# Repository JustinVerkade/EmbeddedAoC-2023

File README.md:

# Embedded-AoC "Yuki"<br />
<br />

## Todo<br />
-> Add ESP32 bootloader function in vcom user interface for remote programming.<br />
-> Add system check for ESP32.<br />

## Completed<br />
-> Added a malloc/calloc/clrmem functions to allocate memory from the SRAM block.<br />
-> Configured FMC and linker to include the external memory as SRAM block.<br />
-> Added vcom enable variable so the system can respond to being opend as port.<br />
-> Added intermediate usb layer as the transmit function failed when bizzy without feedback.<br />
-> f_debug function to log FatFs problems to vcom interface.<br />
-> Added system check for SD card.<br />
-> Added system check for SRAM memory.<br />
-> Added system structure for executing AoC puzzles.<br />

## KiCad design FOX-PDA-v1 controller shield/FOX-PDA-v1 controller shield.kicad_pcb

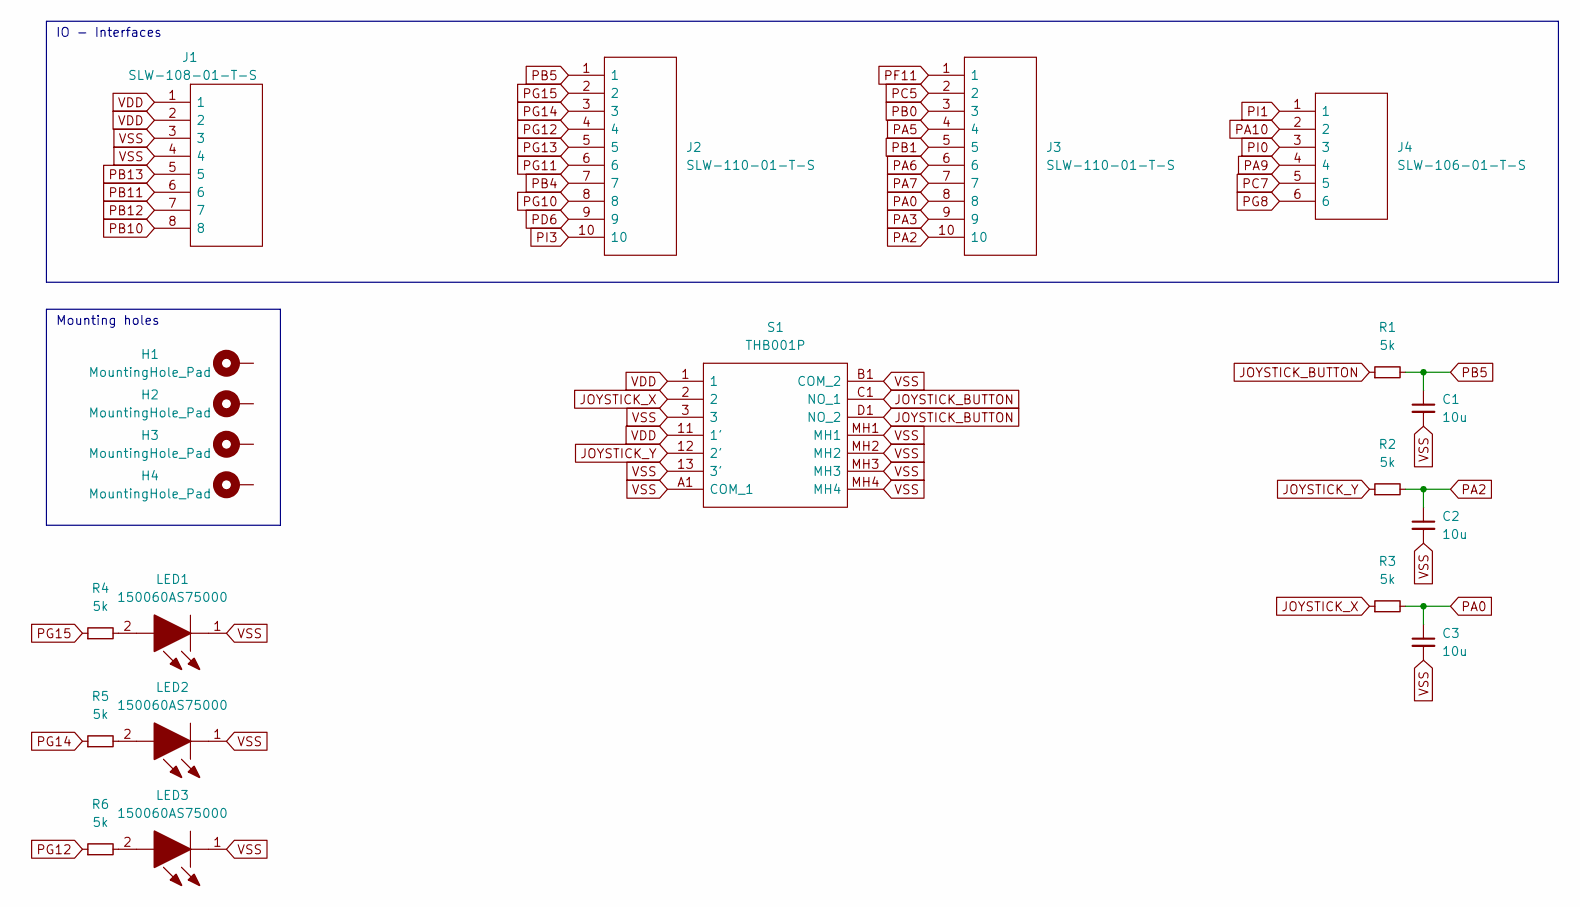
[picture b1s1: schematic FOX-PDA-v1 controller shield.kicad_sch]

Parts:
C1, C2, C3: 10u; C_0805_2012Metric
H1, H2, H3, H4: MountingHole_Pad; MountingHole_3.2mm_M3_Pad_Via
J1: SLW-108-01-T-S; SLW-108-01-X-S; Mouser Part Number 200-SLW10801TS
J2, J3: SLW-110-01-T-S; SLW-110-01-X-S; Mouser Part Number 200-SLW11001TS
J4: SLW-106-01-T-S; SLW-106-01-X-S; Mouser Part Number 200-SLW10601TS
LED1, LED2, LED3: 150060AS75000; LEDC1608X80N; Mouser Part Number 710-150060AS75000
R1, R2, R3, R4, R5, R6: 5k; R_0805_2012Metric
S1: THB001P; Mouser Part Number 611-THB001P

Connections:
JOYSTICK_BUTTON: R1.1, S1.C1 (NO_1), S1.D1 (NO_2)
JOYSTICK_X: R3.1, S1.2
JOYSTICK_Y: R2.1, S1.12 (2')
unnamed: LED1.2, R4.2
unnamed: LED2.2, R5.2
unnamed: LED3.2, R6.2
PA0: C3.1, J3.8, R3.2
PA2: C2.1, J3.10, R2.2
PA3: J3.9
PA5: J3.4
PA6: J3.6
PA7: J3.7
PA9: J4.4
PA10: J4.2
PB0: J3.3
PB1: J3.5
PB4: J2.7
PB5: C1.1, J2.1, R1.2
PB10: J1.8
PB11: J1.6
PB12: J1.7
PB13: J1.5
PC5: J3.2
PC7: J4.5
PD6: J2.9
PF11: J3.1
PG8: J4.6
PG10: J2.8
PG11: J2.6
PG12: J2.4, R6.1
PG13: J2.5
PG14: J2.3, R5.1
PG15: J2.2, R4.1
PI0: J4.3
PI1: J4.1
PI3: J2.10
VDD: J1.1, J1.2, S1.1, S1.11 (1')
VSS: C1.2, C2.2, C3.2, J1.3, J1.4, LED1.1, LED2.1, LED3.1, S1.3, S1.13 (3'), S1.A1 (COM_1), S1.B1 (COM_2), S1.MH1, S1.MH2, S1.MH3, S1.MH4

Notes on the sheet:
IO - Interfaces
Mounting holes

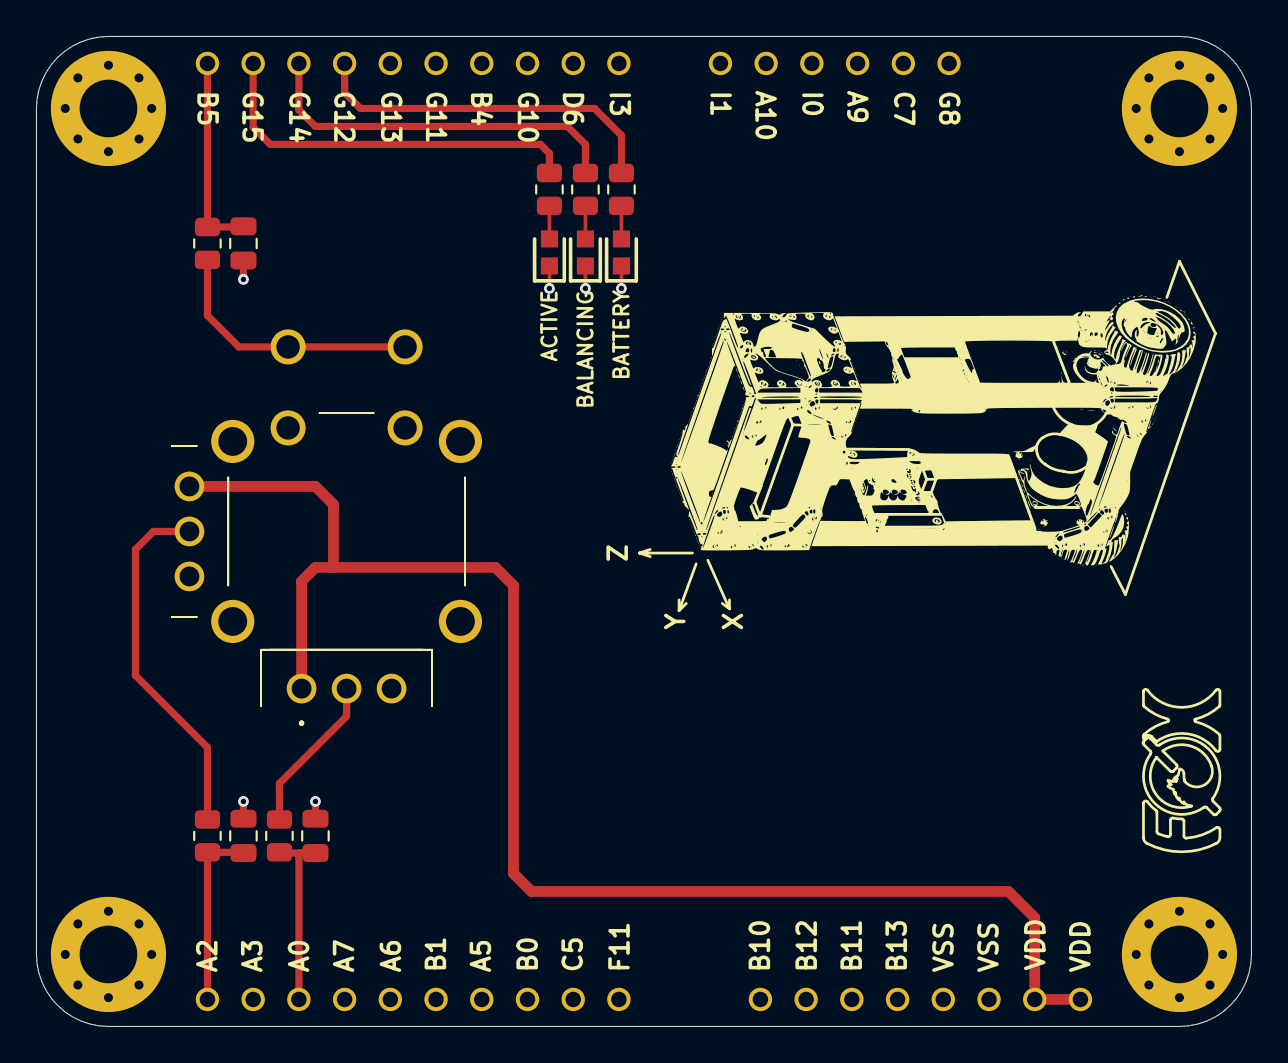
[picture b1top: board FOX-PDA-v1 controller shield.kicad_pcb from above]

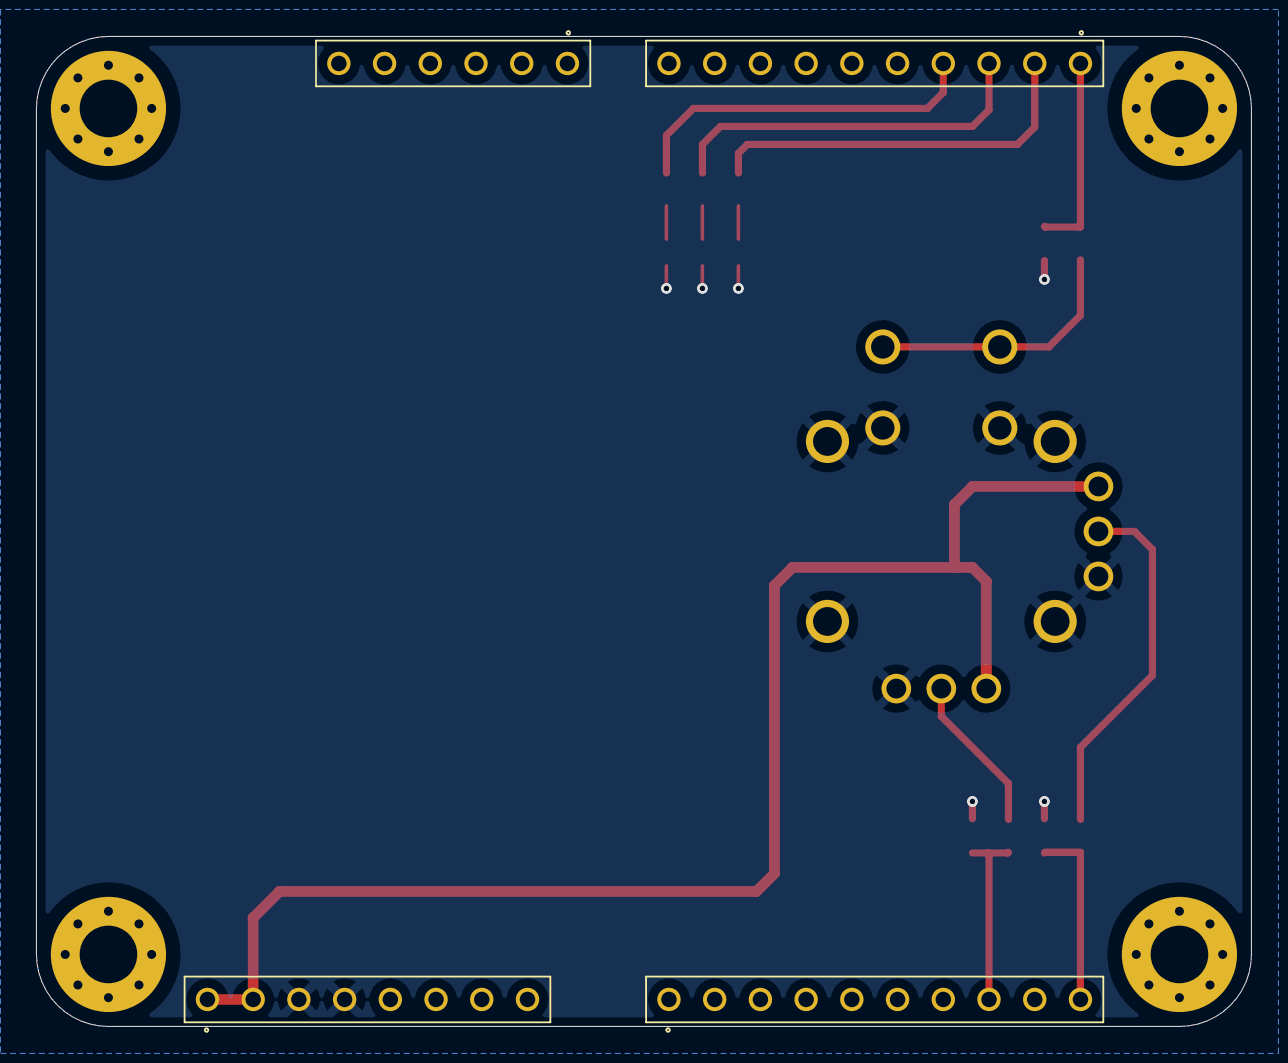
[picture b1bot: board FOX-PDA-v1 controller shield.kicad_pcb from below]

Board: 2 copper layers, 67.5 x 55.0 mm, 21 parts (4 on the bottom side), 14 nets.

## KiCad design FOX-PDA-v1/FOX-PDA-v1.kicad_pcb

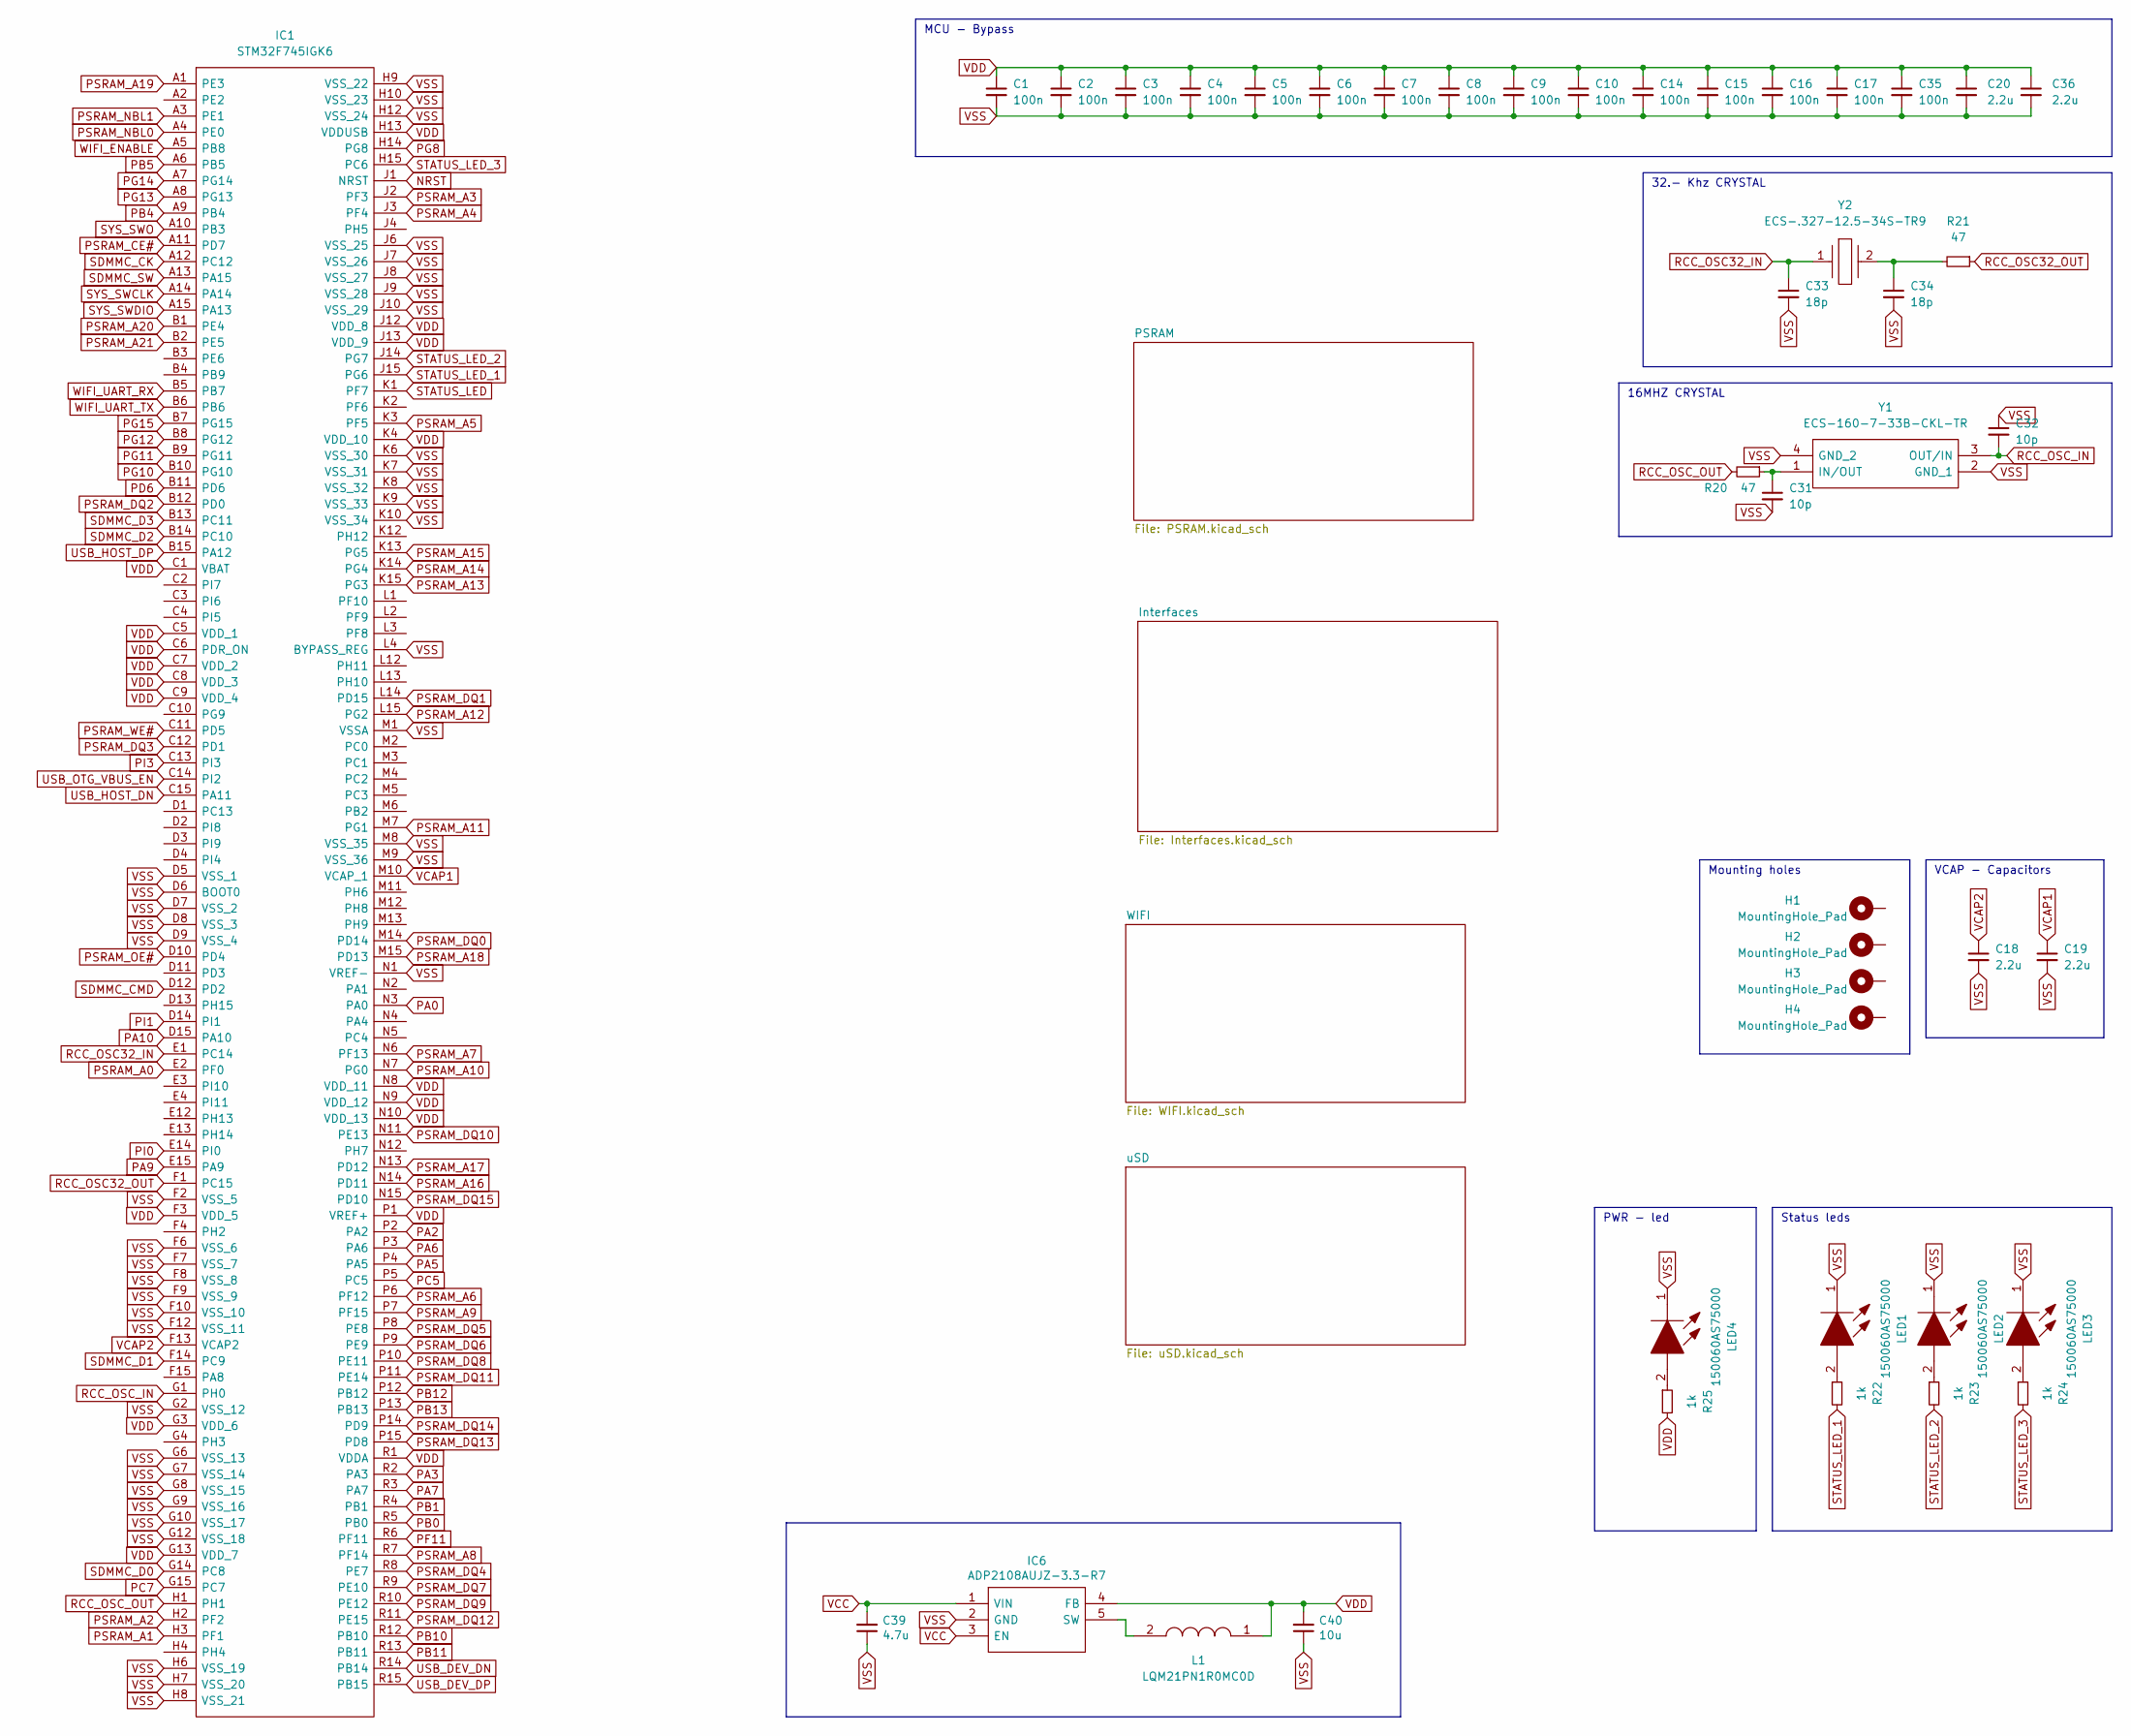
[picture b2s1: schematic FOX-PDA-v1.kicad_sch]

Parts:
C1, C2, C3, C4, C5, C6, C7, C8, C9, C10, C14, C15, C16, C17, C35: 100n; C_0402_1005Metric
C18, C19: 2.2u; C_0402_1005Metric
C20, C36: 2.2u; C_0603_1608Metric
C31, C32: 10p; C_0402_1005Metric
C33, C34: 18p; C_0402_1005Metric
C39: 4.7u; C_0603_1608Metric
C40: 10u; C_0603_1608Metric
H1, H2, H3, H4: MountingHole_Pad; MountingHole_3.2mm_M3_Pad_Via
IC1: STM32F745IGK6; BGA201C65P15X15_1000X1000X60; Mouser Part Number 511-STM32F745IGK6
IC6: ADP2108AUJZ-3.3-R7; SOT95P280X100-5N; Mouser Part Number 584-ADP2108AUJZ3.3R7
L1: LQM21PN1R0MC0D; Mouser Part Number 81-LQM21PN1R0MC0D
LED1, LED2, LED3, LED4: 150060AS75000; LEDC1608X80N; Mouser Part Number 710-150060AS75000
R20, R21: 47; R_0402_1005Metric
R22, R23, R24, R25: 1k; R_0402_1005Metric
Y1: ECS-160-7-33B-CKL-TR; ECS160733BCKLTR; Manufacturer_Part_Number ECS-160-7-33B-CKL-TR
Y2: ECS-.327-12.5-34S-TR9; ECS32712534STR9; Mouser Part Number 520-ECS-32712534STR9

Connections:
NRST: IC1.J1 (NRST); also elsewhere on the board
unnamed: C31.1, R20.1, Y1.1 (IN/OUT)
unnamed: C34.1, R21.2, Y2.2
unnamed: IC6.5 (SW), L1.2
unnamed: LED1.2, R22.1
unnamed: LED2.2, R23.1
unnamed: LED3.2, R24.1
unnamed: LED4.2, R25.1
PA0: IC1.N3 (PA0); also elsewhere on the board
PA2: IC1.P2 (PA2); also elsewhere on the board
PA3: IC1.R2 (PA3); also elsewhere on the board
PA5: IC1.P4 (PA5); also elsewhere on the board
PA6: IC1.P3 (PA6); also elsewhere on the board
PA7: IC1.R3 (PA7); also elsewhere on the board
PA9: IC1.E15 (PA9); also elsewhere on the board
PA10: IC1.D15 (PA10); also elsewhere on the board
PB0: IC1.R5 (PB0); also elsewhere on the board
PB1: IC1.R4 (PB1); also elsewhere on the board
PB4: IC1.A9 (PB4); also elsewhere on the board
PB5: IC1.A6 (PB5); also elsewhere on the board
PB10: IC1.R12 (PB10); also elsewhere on the board
PB11: IC1.R13 (PB11); also elsewhere on the board
PB12: IC1.P12 (PB12); also elsewhere on the board
PB13: IC1.P13 (PB13); also elsewhere on the board
PC5: IC1.P5 (PC5); also elsewhere on the board
PC7: IC1.G15 (PC7); also elsewhere on the board
PD6: IC1.B11 (PD6); also elsewhere on the board
PF11: IC1.R6 (PF11); also elsewhere on the board
PG8: IC1.H14 (PG8); also elsewhere on the board
PG10: IC1.B10 (PG10); also elsewhere on the board
PG11: IC1.B9 (PG11); also elsewhere on the board
PG12: IC1.B8 (PG12); also elsewhere on the board
PG13: IC1.A8 (PG13); also elsewhere on the board
PG14: IC1.A7 (PG14); also elsewhere on the board
PG15: IC1.B7 (PG15); also elsewhere on the board
PI0: IC1.E14 (PI0); also elsewhere on the board
PI1: IC1.D14 (PI1); also elsewhere on the board
PI3: IC1.C13 (PI3); also elsewhere on the board
PSRAM_A0: IC1.E2 (PF0); also elsewhere on the board
PSRAM_A1: IC1.H3 (PF1); also elsewhere on the board
PSRAM_A2: IC1.H2 (PF2); also elsewhere on the board
PSRAM_A3: IC1.J2 (PF3); also elsewhere on the board
PSRAM_A4: IC1.J3 (PF4); also elsewhere on the board
PSRAM_A5: IC1.K3 (PF5); also elsewhere on the board
PSRAM_A6: IC1.P6 (PF12); also elsewhere on the board
PSRAM_A7: IC1.N6 (PF13); also elsewhere on the board
PSRAM_A8: IC1.R7 (PF14); also elsewhere on the board
PSRAM_A9: IC1.P7 (PF15); also elsewhere on the board
PSRAM_A10: IC1.N7 (PG0); also elsewhere on the board
PSRAM_A11: IC1.M7 (PG1); also elsewhere on the board
PSRAM_A12: IC1.L15 (PG2); also elsewhere on the board
PSRAM_A13: IC1.K15 (PG3); also elsewhere on the board
PSRAM_A14: IC1.K14 (PG4); also elsewhere on the board
PSRAM_A15: IC1.K13 (PG5); also elsewhere on the board
PSRAM_A16: IC1.N14 (PD11); also elsewhere on the board
PSRAM_A17: IC1.N13 (PD12); also elsewhere on the board
PSRAM_A18: IC1.M15 (PD13); also elsewhere on the board
PSRAM_A19: IC1.A1 (PE3); also elsewhere on the board
PSRAM_A20: IC1.B1 (PE4); also elsewhere on the board
PSRAM_A21: IC1.B2 (PE5); also elsewhere on the board
PSRAM_CE#: IC1.A11 (PD7); also elsewhere on the board
PSRAM_DQ0: IC1.M14 (PD14); also elsewhere on the board
PSRAM_DQ1: IC1.L14 (PD15); also elsewhere on the board
PSRAM_DQ2: IC1.B12 (PD0); also elsewhere on the board
PSRAM_DQ3: IC1.C12 (PD1); also elsewhere on the board
PSRAM_DQ4: IC1.R8 (PE7); also elsewhere on the board
PSRAM_DQ5: IC1.P8 (PE8); also elsewhere on the board
PSRAM_DQ6: IC1.P9 (PE9); also elsewhere on the board
PSRAM_DQ7: IC1.R9 (PE10); also elsewhere on the board
PSRAM_DQ8: IC1.P10 (PE11); also elsewhere on the board
PSRAM_DQ9: IC1.R10 (PE12); also elsewhere on the board
PSRAM_DQ10: IC1.N11 (PE13); also elsewhere on the board
PSRAM_DQ11: IC1.P11 (PE14); also elsewhere on the board
PSRAM_DQ12: IC1.R11 (PE15); also elsewhere on the board
PSRAM_DQ13: IC1.P15 (PD8); also elsewhere on the board
PSRAM_DQ14: IC1.P14 (PD9); also elsewhere on the board
PSRAM_DQ15: IC1.N15 (PD10); also elsewhere on the board
PSRAM_NBL0: IC1.A4 (PE0); also elsewhere on the board
PSRAM_NBL1: IC1.A3 (PE1); also elsewhere on the board
PSRAM_OE#: IC1.D10 (PD4); also elsewhere on the board
PSRAM_WE#: IC1.C11 (PD5); also elsewhere on the board
RCC_OSC32_IN: C33.1, IC1.E1 (PC14), Y2.1
RCC_OSC32_OUT: IC1.F1 (PC15), R21.1
RCC_OSC_IN: C32.2, IC1.G1 (PH0), Y1.3 (OUT/IN)
RCC_OSC_OUT: IC1.H1, R20.2
SDMMC_CK: IC1.A12 (PC12); also elsewhere on the board
SDMMC_CMD: IC1.D12 (PD2); also elsewhere on the board
SDMMC_D0: IC1.G14 (PC8); also elsewhere on the board
SDMMC_D1: IC1.F14 (PC9); also elsewhere on the board
SDMMC_D2: IC1.B14 (PC10); also elsewhere on the board
SDMMC_D3: IC1.B13 (PC11); also elsewhere on the board
SDMMC_SW: IC1.A13 (PA15); also elsewhere on the board
STATUS_LED: IC1.K1 (PF7)
STATUS_LED_1: IC1.J15 (PG6), R22.2
STATUS_LED_2: IC1.J14 (PG7), R23.2
STATUS_LED_3: IC1.H15 (PC6), R24.2
SYS_SWCLK: IC1.A14; also elsewhere on the board
SYS_SWDIO: IC1.A15 (PA13); also elsewhere on the board
SYS_SWO: IC1.A10 (PB3); also elsewhere on the board
USB_DEV_DN: IC1.R14 (PB14); also elsewhere on the board
USB_DEV_DP: IC1.R15 (PB15); also elsewhere on the board
USB_HOST_DN: IC1.C15 (PA11); also elsewhere on the board
USB_HOST_DP: IC1.B15 (PA12); also elsewhere on the board
USB_OTG_VBUS_EN: IC1.C14 (PI2)
VCAP1: C19.1, IC1.M10 (VCAP_1)
VCAP2: C18.1, IC1.F13 (VCAP2)
VCC: C39.2, IC6.1 (VIN), IC6.3 (EN); also elsewhere on the board
VDD: C1.1, C2.1, C3.1, C4.1, C5.1, C6.1, C7.1, C8.1, C9.1, C10.1, C14.1, C15.1, C16.1, C17.1, C20.1, C35.1, C36.1, C40.2, IC1.C1 (VBAT), IC1.C5 (VDD_1), IC1.C6 (PDR_ON), IC1.C7 (VDD_2), IC1.C8 (VDD_3), IC1.C9 (VDD_4), IC1.F3 (VDD_5), IC1.G3 (VDD_6), IC1.G13 (VDD_7), IC1.H13 (VDDUSB), IC1.J12 (VDD_8), IC1.J13 (VDD_9), IC1.K4 (VDD_10), IC1.N8 (VDD_11), IC1.N9 (VDD_12), IC1.N10 (VDD_13), IC1.P1 (VREF+), IC1.R1 (VDDA), IC6.4 (FB), L1.1, R25.2; also elsewhere on the board
VSS: C1.2, C2.2, C3.2, C4.2, C5.2, C6.2, C7.2, C8.2, C9.2, C10.2, C14.2, C15.2, C16.2, C17.2, C18.2, C19.2, C20.2, C31.2, C32.1, C33.2, C34.2, C35.2, C36.2, C39.1, C40.1, IC1.D5 (VSS_1), IC1.D6 (BOOT0), IC1.D7 (VSS_2), IC1.D8 (VSS_3), IC1.D9 (VSS_4), IC1.F2 (VSS_5), IC1.F6 (VSS_6), IC1.F7 (VSS_7), IC1.F8 (VSS_8), IC1.F9 (VSS_9), IC1.F10 (VSS_10), IC1.F12 (VSS_11), IC1.G2 (VSS_12), IC1.G6 (VSS_13), IC1.G7 (VSS_14), IC1.G8 (VSS_15), IC1.G9 (VSS_16), IC1.G10 (VSS_17), IC1.G12 (VSS_18), IC1.H6 (VSS_19), IC1.H7 (VSS_20), IC1.H8 (VSS_21), IC1.H9 (VSS_22), IC1.H10 (VSS_23), IC1.H12 (VSS_24), IC1.J6 (VSS_25), IC1.J7 (VSS_26), IC1.J8 (VSS_27), IC1.J9 (VSS_28), IC1.J10 (VSS_29), IC1.K6 (VSS_30), IC1.K7 (VSS_31), IC1.K8 (VSS_32), IC1.K9 (VSS_33), IC1.K10 (VSS_34), IC1.L4 (BYPASS_REG), IC1.M1 (VSSA), IC1.M8 (VSS_35), IC1.M9 (VSS_36), IC1.N1 (VREF-), IC6.2 (GND), LED1.1, LED2.1, LED3.1, LED4.1, Y1.2 (GND_1), Y1.4 (GND_2); also elsewhere on the board
WIFI_ENABLE: IC1.A5 (PB8); also elsewhere on the board
WIFI_UART_RX: IC1.B5 (PB7); also elsewhere on the board
WIFI_UART_TX: IC1.B6; also elsewhere on the board

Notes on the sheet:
16MHZ CRYSTAL
32.- Khz CRYSTAL
PWR - led
Status leds
VCAP - Capacitors
Mounting holes
MCU - Bypass

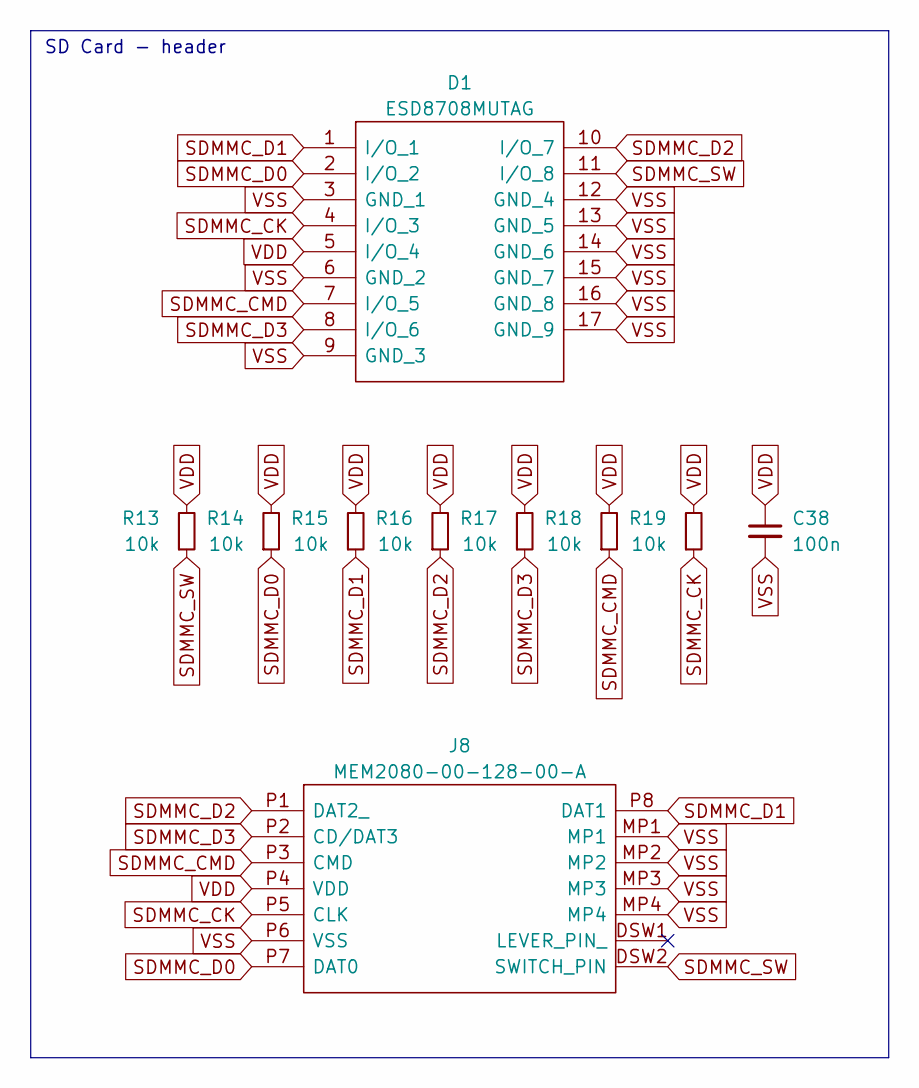
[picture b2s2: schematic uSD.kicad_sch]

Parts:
C38: 100n; C_0402_1005Metric
D1: ESD8708MUTAG; Mouser Part Number 863-ESD8708MUTAG
J8: MEM2080-00-128-00-A; MEM20800012800A; Mouser Part Number 640-MEM2080-0012800A
R13, R14, R15, R16, R17, R18, R19: 10k; R_0402_1005Metric

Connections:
SDMMC_CK: D1.4 (I/O_3), J8.P5 (CLK), R19.1; also elsewhere on the board
SDMMC_CMD: D1.7 (I/O_5), J8.P3 (CMD), R18.1; also elsewhere on the board
SDMMC_D0: D1.2 (I/O_2), J8.P7 (DAT0), R14.1; also elsewhere on the board
SDMMC_D1: D1.1 (I/O_1), J8.P8 (DAT1), R15.1; also elsewhere on the board
SDMMC_D2: D1.10 (I/O_7), J8.P1 (DAT2_), R16.1; also elsewhere on the board
SDMMC_D3: D1.8 (I/O_6), J8.P2 (CD/DAT3), R17.1; also elsewhere on the board
SDMMC_SW: D1.11 (I/O_8), J8.DSW2 (SWITCH_PIN), R13.1; also elsewhere on the board
VDD: C38.1, D1.5 (I/O_4), J8.P4 (VDD), R13.2, R14.2, R15.2, R16.2, R17.2, R18.2, R19.2; also elsewhere on the board
VSS: C38.2, D1.3 (GND_1), D1.6 (GND_2), D1.9 (GND_3), D1.12 (GND_4), D1.13 (GND_5), D1.14 (GND_6), D1.15 (GND_7), D1.16 (GND_8), D1.17 (GND_9), J8.MP1, J8.MP2, J8.MP3, J8.MP4, J8.P6 (VSS); also elsewhere on the board

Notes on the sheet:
SD Card - header

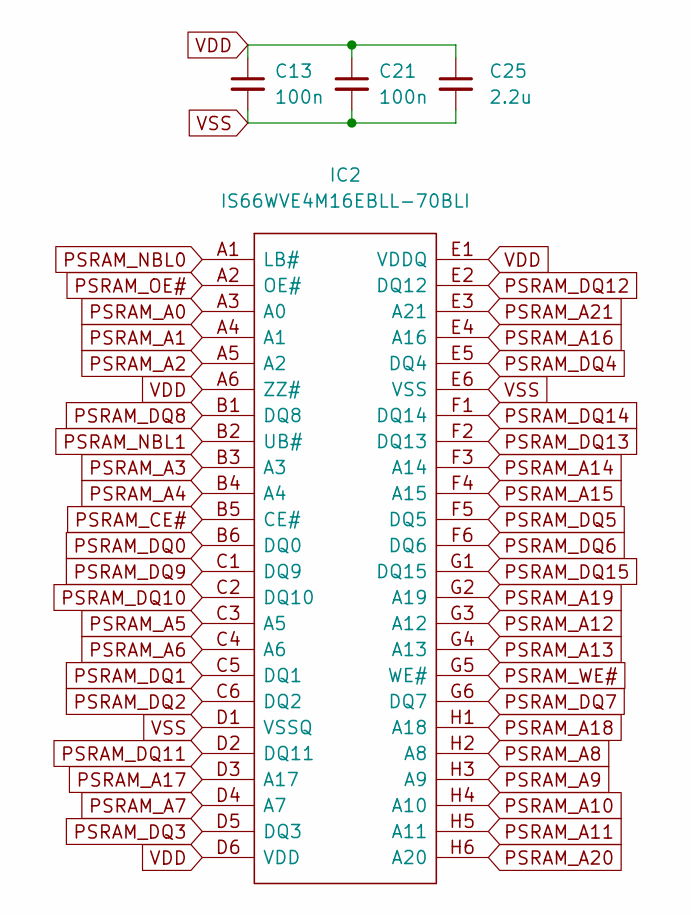
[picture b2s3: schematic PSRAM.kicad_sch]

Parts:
C13, C21: 100n; C_0402_1005Metric
C25: 2.2u; C_0603_1608Metric
IC2: IS66WVE4M16EBLL-70BLI; BGA48C75P6X8_600X800X120; Mouser Part Number 870-66E4M16EBLL70BLI

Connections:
PSRAM_A0: IC2.A3 (A0); also elsewhere on the board
PSRAM_A1: IC2.A4 (A1); also elsewhere on the board
PSRAM_A2: IC2.A5 (A2); also elsewhere on the board
PSRAM_A3: IC2.B3 (A3); also elsewhere on the board
PSRAM_A4: IC2.B4 (A4); also elsewhere on the board
PSRAM_A5: IC2.C3 (A5); also elsewhere on the board
PSRAM_A6: IC2.C4 (A6); also elsewhere on the board
PSRAM_A7: IC2.D4 (A7); also elsewhere on the board
PSRAM_A8: IC2.H2 (A8); also elsewhere on the board
PSRAM_A9: IC2.H3 (A9); also elsewhere on the board
PSRAM_A10: IC2.H4 (A10); also elsewhere on the board
PSRAM_A11: IC2.H5 (A11); also elsewhere on the board
PSRAM_A12: IC2.G3 (A12); also elsewhere on the board
PSRAM_A13: IC2.G4 (A13); also elsewhere on the board
PSRAM_A14: IC2.F3 (A14); also elsewhere on the board
PSRAM_A15: IC2.F4 (A15); also elsewhere on the board
PSRAM_A16: IC2.E4 (A16); also elsewhere on the board
PSRAM_A17: IC2.D3 (A17); also elsewhere on the board
PSRAM_A18: IC2.H1 (A18); also elsewhere on the board
PSRAM_A19: IC2.G2 (A19); also elsewhere on the board
PSRAM_A20: IC2.H6 (A20); also elsewhere on the board
PSRAM_A21: IC2.E3 (A21); also elsewhere on the board
PSRAM_CE#: IC2.B5 (CE#); also elsewhere on the board
PSRAM_DQ0: IC2.B6 (DQ0); also elsewhere on the board
PSRAM_DQ1: IC2.C5 (DQ1); also elsewhere on the board
PSRAM_DQ2: IC2.C6 (DQ2); also elsewhere on the board
PSRAM_DQ3: IC2.D5 (DQ3); also elsewhere on the board
PSRAM_DQ4: IC2.E5 (DQ4); also elsewhere on the board
PSRAM_DQ5: IC2.F5 (DQ5); also elsewhere on the board
PSRAM_DQ6: IC2.F6 (DQ6); also elsewhere on the board
PSRAM_DQ7: IC2.G6 (DQ7); also elsewhere on the board
PSRAM_DQ8: IC2.B1 (DQ8); also elsewhere on the board
PSRAM_DQ9: IC2.C1 (DQ9); also elsewhere on the board
PSRAM_DQ10: IC2.C2 (DQ10); also elsewhere on the board
PSRAM_DQ11: IC2.D2 (DQ11); also elsewhere on the board
PSRAM_DQ12: IC2.E2 (DQ12); also elsewhere on the board
PSRAM_DQ13: IC2.F2 (DQ13); also elsewhere on the board
PSRAM_DQ14: IC2.F1 (DQ14); also elsewhere on the board
PSRAM_DQ15: IC2.G1 (DQ15); also elsewhere on the board
PSRAM_NBL0: IC2.A1 (LB#); also elsewhere on the board
PSRAM_NBL1: IC2.B2 (UB#); also elsewhere on the board
PSRAM_OE#: IC2.A2 (OE#); also elsewhere on the board
PSRAM_WE#: IC2.G5 (WE#); also elsewhere on the board
VDD: C13.1, C21.1, C25.1, IC2.A6 (ZZ#), IC2.D6 (VDD), IC2.E1 (VDDQ); also elsewhere on the board
VSS: C13.2, C21.2, C25.2, IC2.D1 (VSSQ), IC2.E6 (VSS); also elsewhere on the board

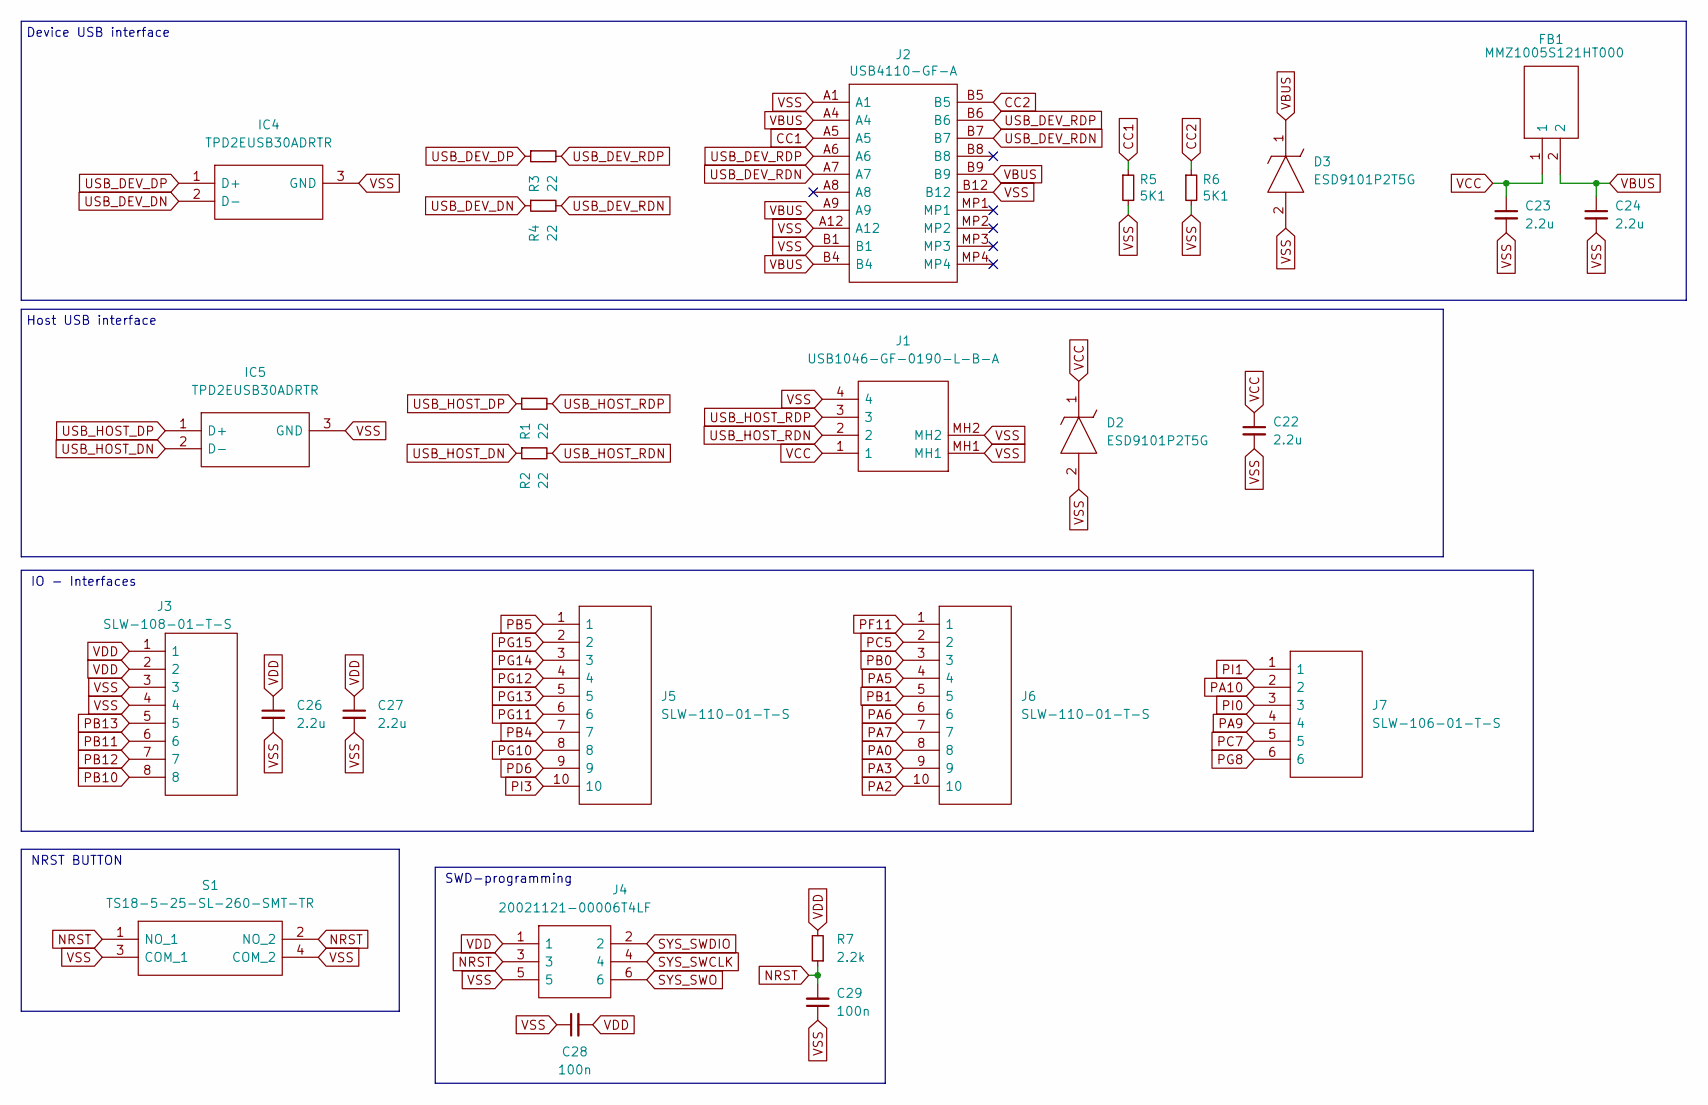
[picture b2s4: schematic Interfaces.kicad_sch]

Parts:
C22, C23, C24, C26, C27: 2.2u; C_0603_1608Metric
C28, C29: 100n; C_0402_1005Metric
D2, D3: ESD9101P2T5G; SODFL1006X40N; Mouser Part Number 863-ESD9101P2T5G
FB1: MMZ1005S121HT000; BEADC1005X55N; Mouser Part Number 810-MMZ1005S121HT000
IC4, IC5: TPD2EUSB30ADRTR; SOT35P100X50-3N; Mouser Part Number 595-TPD2EUSB30ADRTR
J1: USB1046-GF-0190-L-B-A; USB1046GF0190LBA; Mouser Part Number 640-USB1046GF0190LBA
J2: USB4110-GF-A; USB4110GFA; Mouser Part Number 640-USB4110-GF-A
J3: SLW-108-01-T-S; SLW-108-01-X-S; Mouser Part Number 200-SLW10801TS
J4: 20021121-00006T4LF; HUSSP6W41P127_2X3_381X343X440P; Mouser Part Number 649-221121-00006T4LF
J5, J6: SLW-110-01-T-S; SLW-110-01-X-S; Mouser Part Number 200-SLW11001TS
J7: SLW-106-01-T-S; SLW-106-01-X-S; Mouser Part Number 200-SLW10601TS
R1, R2, R3, R4: 22; R_0402_1005Metric
R5, R6: 5K1; R_0402_1005Metric
R7: 2.2k; R_0402_1005Metric
S1: TS18-5-25-SL-260-SMT-TR; TS18525SL260SMTTR; Mouser Part Number 179-TS18525SL260SMTT

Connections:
CC1: J2.A5, R5.1
CC2: J2.B5, R6.1
NRST: C29.2, J4.3, R7.1, S1.1 (NO_1), S1.2 (NO_2); also elsewhere on the board
PA0: J6.8; also elsewhere on the board
PA2: J6.10; also elsewhere on the board
PA3: J6.9; also elsewhere on the board
PA5: J6.4; also elsewhere on the board
PA6: J6.6; also elsewhere on the board
PA7: J6.7; also elsewhere on the board
PA9: J7.4; also elsewhere on the board
PA10: J7.2; also elsewhere on the board
PB0: J6.3; also elsewhere on the board
PB1: J6.5; also elsewhere on the board
PB4: J5.7; also elsewhere on the board
PB5: J5.1; also elsewhere on the board
PB10: J3.8; also elsewhere on the board
PB11: J3.6; also elsewhere on the board
PB12: J3.7; also elsewhere on the board
PB13: J3.5; also elsewhere on the board
PC5: J6.2; also elsewhere on the board
PC7: J7.5; also elsewhere on the board
PD6: J5.9; also elsewhere on the board
PF11: J6.1; also elsewhere on the board
PG8: J7.6; also elsewhere on the board
PG10: J5.8; also elsewhere on the board
PG11: J5.6; also elsewhere on the board
PG12: J5.4; also elsewhere on the board
PG13: J5.5; also elsewhere on the board
PG14: J5.3; also elsewhere on the board
PG15: J5.2; also elsewhere on the board
PI0: J7.3; also elsewhere on the board
PI1: J7.1; also elsewhere on the board
PI3: J5.10; also elsewhere on the board
SYS_SWCLK: J4.4; also elsewhere on the board
SYS_SWDIO: J4.2; also elsewhere on the board
SYS_SWO: J4.6; also elsewhere on the board
USB_DEV_DN: IC4.2 (D-), R4.1; also elsewhere on the board
USB_DEV_DP: IC4.1 (D+), R3.1; also elsewhere on the board
USB_DEV_RDN: J2.A7, J2.B7, R4.2
USB_DEV_RDP: J2.A6, J2.B6, R3.2
USB_HOST_DN: IC5.2 (D-), R2.1; also elsewhere on the board
USB_HOST_DP: IC5.1 (D+), R1.1; also elsewhere on the board
USB_HOST_RDN: J1.2, R2.2
USB_HOST_RDP: J1.3, R1.2
VBUS: C24.1, D3.1, FB1.2, J2.A4, J2.A9, J2.B4, J2.B9
VCC: C22.1, C23.1, D2.1, FB1.1, J1.1; also elsewhere on the board
VDD: C26.1, C27.1, C28.2, J3.1, J3.2, J4.1, R7.2; also elsewhere on the board
VSS: C22.2, C23.2, C24.2, C26.2, C27.2, C28.1, C29.1, D2.2, D3.2, IC4.3 (GND), IC5.3 (GND), J1.4, J1.MH1, J1.MH2, J2.A1, J2.A12, J2.B1, J2.B12, J3.3, J3.4, J4.5, R5.2, R6.2, S1.3 (COM_1), S1.4 (COM_2); also elsewhere on the board

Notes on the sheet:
NRST BUTTON
Device USB interface
SWD-programming
Host USB interface
IO - Interfaces
